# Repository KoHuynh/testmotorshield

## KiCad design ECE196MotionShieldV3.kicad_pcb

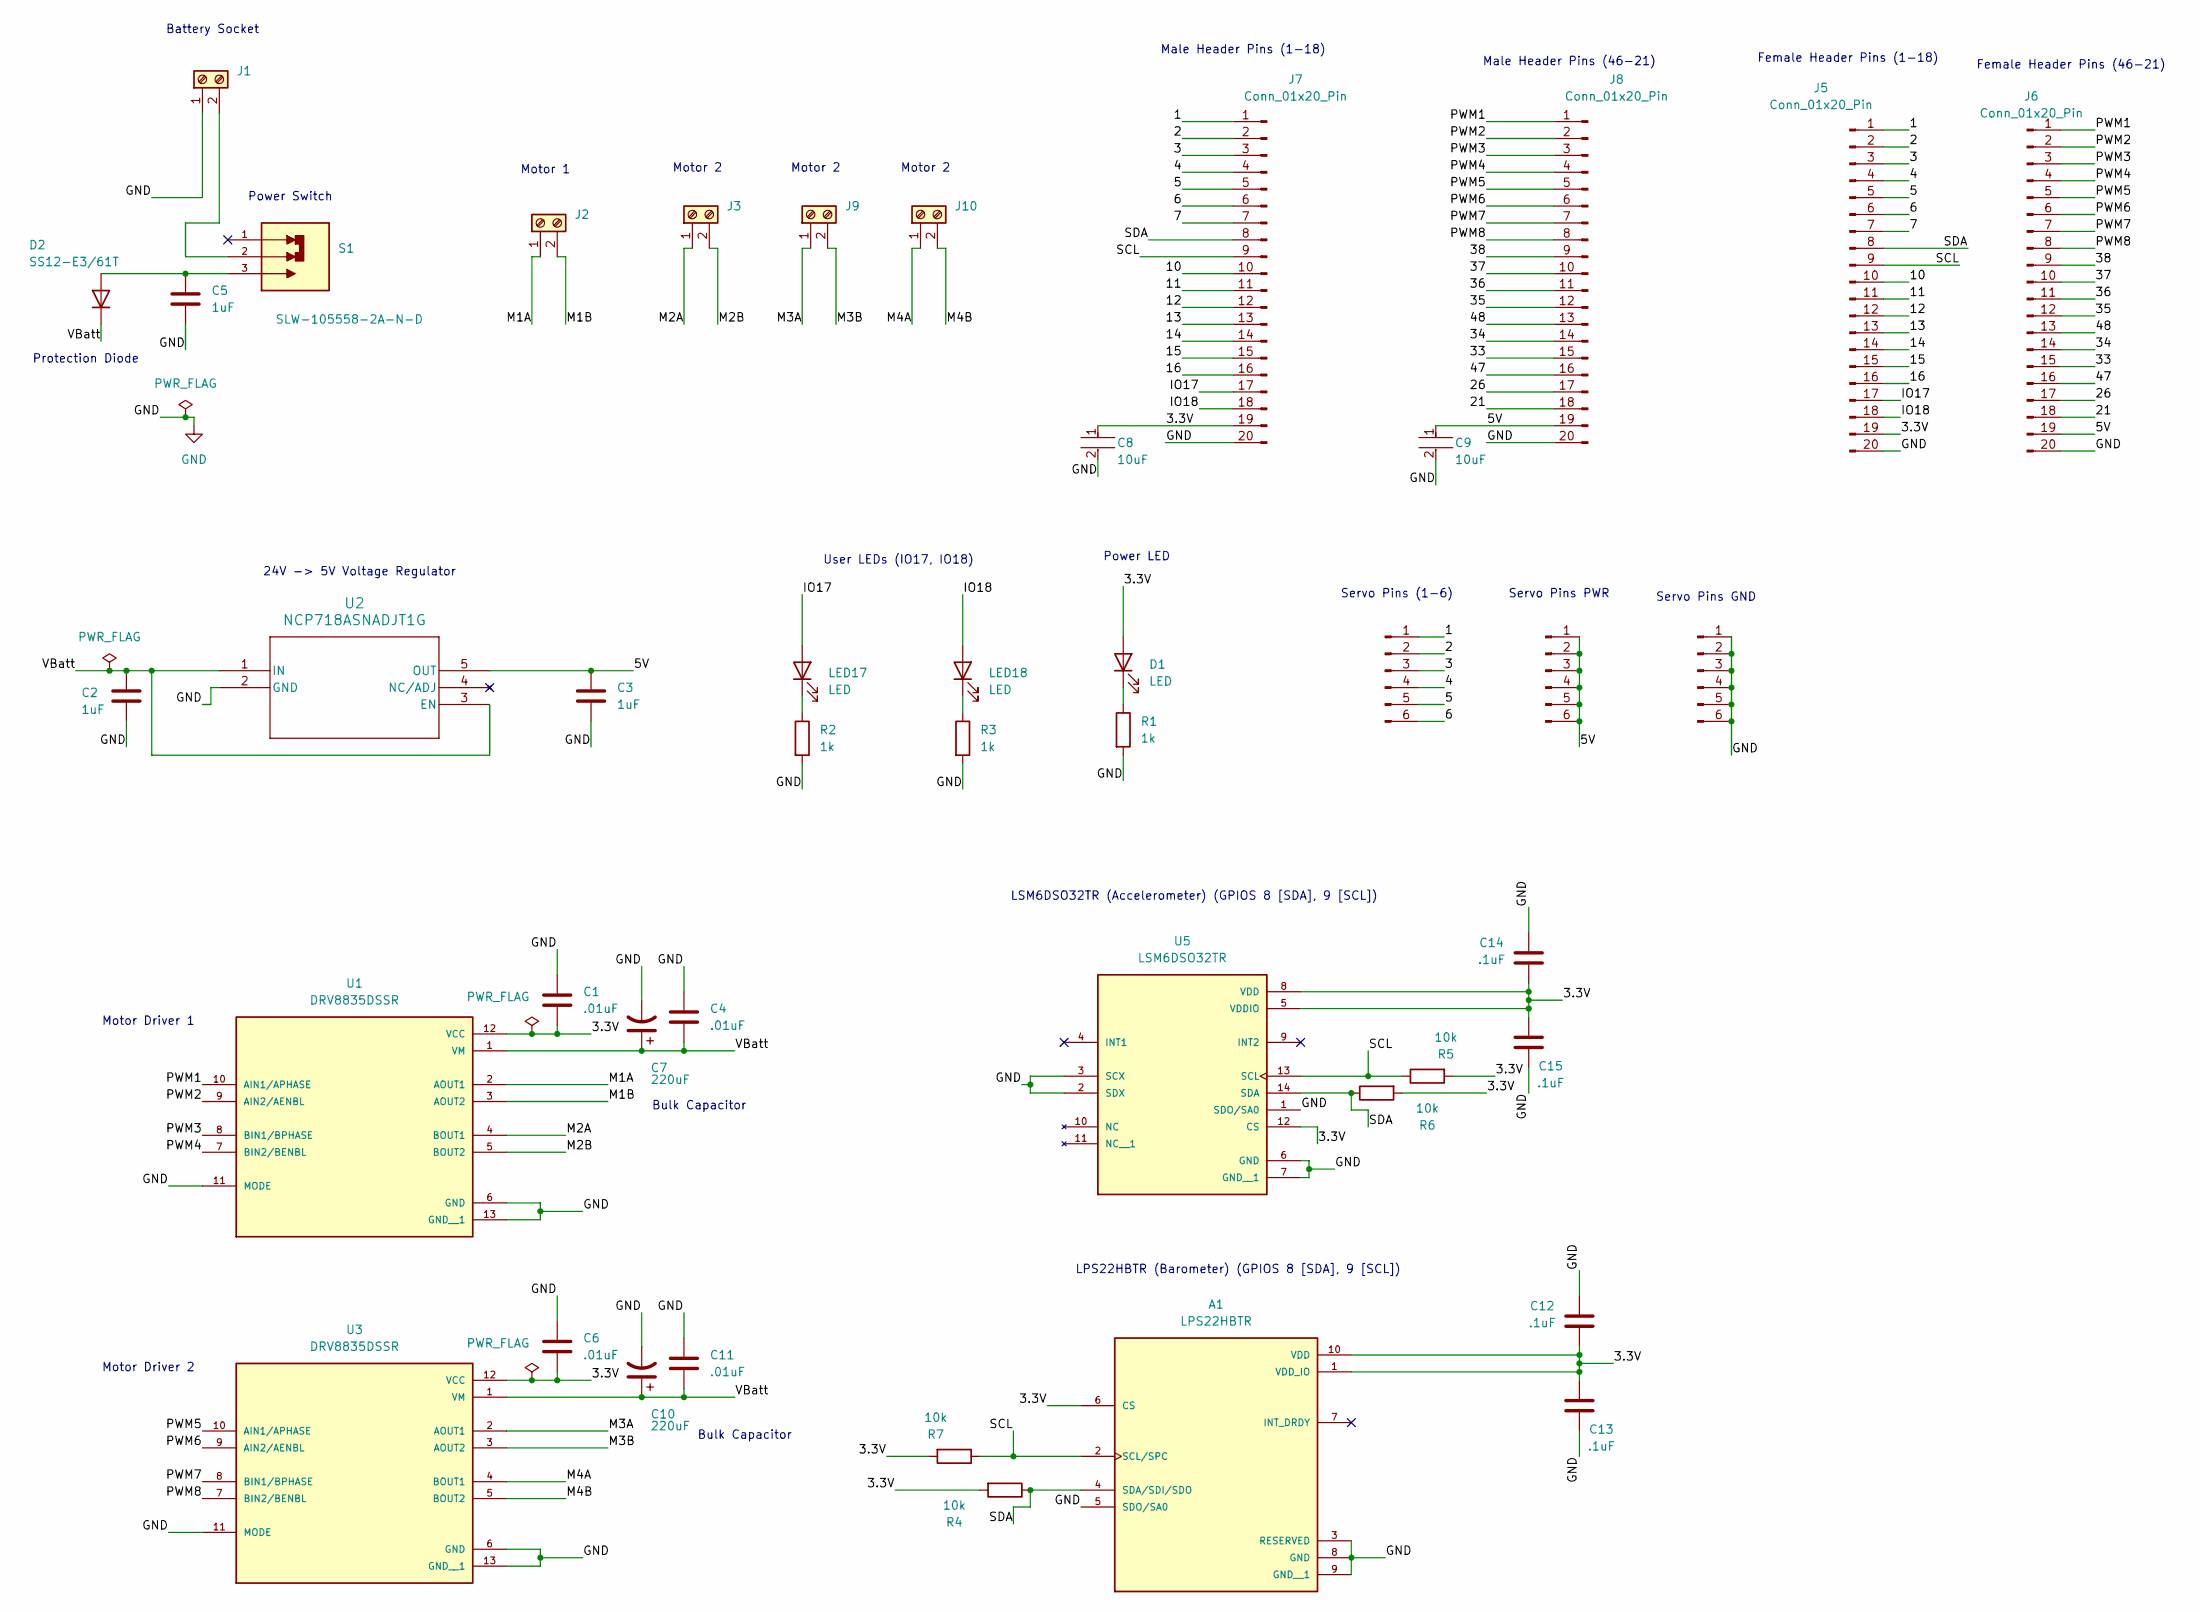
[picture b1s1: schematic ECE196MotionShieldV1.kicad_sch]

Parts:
A1: LPS22HBTR; PQFN50P200X200X80-10N; PARTREV 6
C1, C4, C6, C11: .01uF; C_0201_0603Metric
C2, C3, C5: 1uF; C_0201_0603Metric
C7, C10: 220uF; WCAP-ASLI_6.3X7.7_DXL_
C8, C9: 10uF; C_0201_0603Metric; VOLTAGE 6.3V; VOLTAGE RATING (DC) 6.3V
C12, C13, C14, C15: .1uF; C_0201_0603Metric
D1: LED; LED_0805_2012Metric
D2: SS12-E3/61T; SMADO-214AC_VIS
J1, J2, J3, J9, J10: Screw_Terminal_01x02; CONN_OSTVN02A150_OST
J4, J11, J12: Conn_01x06_Pin; PinHeader_1x06_P2.54mm_Vertical
J5, J6: Conn_01x20_Pin; PinSocket_1x20_P2.54mm_Vertical
J7, J8: Conn_01x20_Pin; PinHeader_1x20_P2.54mm_Vertical
LED17, LED18: LED; LED_0805_2012Metric
R1, R2, R3: 1k; R_0201_0603Metric
R4, R5, R6, R7: 10k; R_0201_0603Metric
S1: SLW-105558-2A-N-D; SW_SLW-105558-2A-N-D; PARTREV 1.01
U1, U3: DRV8835DSSR; SON50P300X200X80-13N; PARTREV H
U2: NCP718ASNADJT1G; TSOT-23-5_2P9X1P6_ONS
U5: LSM6DSO32TR; XDCR_LSM6DSO32TR; PARTREV 1

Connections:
/1: J4.1, J5.1, J7.1
/2: J4.2, J5.2, J7.2
/3: J4.3, J5.3, J7.3
/3.3V: A1.1 (VDD_IO), A1.6 (CS), A1.10 (VDD), C1.1, C6.1, C8.1, C12.1, C13.1, C14.1, C15.1, D1.2 (A), J5.19, J7.19, R4.2, R5.2, R6.2, R7.2, U1.12 (VCC), U3.12 (VCC), U5.5 (VDDIO), U5.8 (VDD), U5.12 (CS)
/4: J4.4, J5.4, J7.4
/5: J4.5, J5.5, J7.5
/5V: C3.2, C9.1, J6.19, J8.19, J11.1, J11.2, J11.3, J11.4, J11.5, J11.6, U2.5 (OUT)
/6: J4.6, J5.6, J7.6
/7: J5.7, J7.7
/10: J5.10, J7.10
/11: J5.11, J7.11
/12: J5.12, J7.12
/13: J5.13, J7.13
/14: J5.14, J7.14
/15: J5.15, J7.15
/16: J5.16, J7.16
/21: J6.18, J8.18
/26: J6.17, J8.17
/33: J6.15, J8.15
/34: J6.14, J8.14
/35: J6.12, J8.12
/36: J6.11, J8.11
/37: J6.10, J8.10
/38: J6.9, J8.9
/47: J6.16, J8.16
/48: J6.13, J8.13
/IO17: J5.17, J7.17, LED17.2 (A)
/IO18: J5.18, J7.18, LED18.2 (A)
/M1A: J2.1, U1.2 (AOUT1)
/M1B: J2.2, U1.3 (AOUT2)
/M2A: J3.1, U1.4 (BOUT1)
/M2B: J3.2, U1.5 (BOUT2)
/M3A: J9.1, U3.2 (AOUT1)
/M3B: J9.2, U3.3 (AOUT2)
/M4A: J10.1, U3.4 (BOUT1)
/M4B: J10.2, U3.5 (BOUT2)
/PWM1: J6.1, J8.1, U1.10 (AIN1/APHASE)
/PWM2: J6.2, J8.2, U1.9 (AIN2/AENBL)
/PWM3: J6.3, J8.3, U1.8 (BIN1/BPHASE)
/PWM4: J6.4, J8.4, U1.7 (BIN2/BENBL)
/PWM5: J6.5, J8.5, U3.10 (AIN1/APHASE)
/PWM6: J6.6, J8.6, U3.9 (AIN2/AENBL)
/PWM7: J6.7, J8.7, U3.8 (BIN1/BPHASE)
/PWM8: J6.8, J8.8, U3.7 (BIN2/BENBL)
/SCL: A1.2 (SCL/SPC), J5.9, J7.9, R5.1, R7.1, U5.13 (SCL)
/SDA: A1.4 (SDA/SDI/SDO), J5.8, J7.8, R4.1, R6.1, U5.14 (SDA)
/VBatt: C2.1, C4.1, C7.1, C10.1, C11.1, D2.1 (K), U1.1 (VM), U2.1 (IN), U2.3 (EN), U3.1 (VM)
GND: A1.3 (RESERVED), A1.5 (SDO/SA0), A1.8 (GND), A1.9 (GND__1), C1.2, C2.2, C3.1, C4.2, C5.1, C6.2, C7.2, C8.2, C9.2, C10.2, C11.2, C12.2, C13.2, C14.2, C15.2, J1.1, J5.20, J6.20, J7.20, J8.20, J12.1, J12.2, J12.3, J12.4, J12.5, J12.6, R1.2, R2.2, R3.2, U1.6 (GND), U1.11 (MODE), U1.13 (GND__1), U2.2 (GND), U3.6 (GND), U3.11 (MODE), U3.13 (GND__1), U5.1 (SDO/SA0), U5.2 (SDX), U5.3 (SCX), U5.6 (GND), U5.7 (GND__1); also elsewhere on the board
unnamed: D1.1 (K), R1.1
unnamed: C5.2, D2.2 (A), S1.3
unnamed 50: J1.2, S1.2; also elsewhere on the board
unnamed: LED17.1 (K), R2.1
unnamed: LED18.1 (K), R3.1

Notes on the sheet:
Servo Pins GND
Power LED
Protection Diode
Servo Pins PWR
Motor 2
User LEDs (IO17, IO18)
Motor Driver 2
Female Header Pins (1-18)
Male Header Pins (46-21)
Servo Pins (1-6)
Bulk Capacitor
LSM6DSO32TR (Accelerometer) (GPIOS 8 [SDA], 9 [SCL])
Battery Socket
Male Header Pins (1-18)
LPS22HBTR (Barometer) (GPIOS 8 [SDA], 9 [SCL])
Power Switch
Female Header Pins (46-21)
Motor Driver 1
24V -> 5V Voltage Regulator
Motor 1

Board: 2 copper layers, 45 parts (2 on the bottom side), 53 nets, no tracks yet.

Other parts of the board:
C16: 10uF; C_0603_1608Metric

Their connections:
GND: C16.1; also elsewhere on the board
unnamed 50: C16.2; also elsewhere on the board
